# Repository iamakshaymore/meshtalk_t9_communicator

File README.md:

<div align="center" markdown="1">

<h1>Meshtastic Firmware</h1>

</div>

</div>

<div align="center">
	<a href="https://meshtastic.org">Website</a>
	-
	<a href="https://meshtastic.org/docs/">Documentation</a>
</div>

## Overview

**This is a fork of the official Meshtastic firmware** with custom UI implementation currently working on:
- **Heltec WiFi LoRa 32 V3**
- **Heltec WiFi LoRa 32 V4**
- **MeshTalk T9** (Custom PCB - MESHTASTIC Build-Off 2026 Entry)

This fork adds a custom keyboard-driven UI with T9 input, LoRa network visualization, and message management capabilities using a 4x4 matrix keypad and TFT display.

### Hardware Configuration

#### Heltec V3 Custom Pin Configuration

**TFT Display (ST7789 240x320):**
- CS: GPIO 10
- DC: GPIO 11  
- RST: GPIO 12
- Backlight: GPIO 13
- SPI: VSPI (MOSI: 35, SCK: 36)

**4x4 Matrix Keypad:**
- Rows: GPIO 14, 15, 16, 17
- Cols: GPIO 4, 5, 6, 7

**Power & Battery:**
- VEXT Enable: GPIO 18 (active low)
- Battery Pin: GPIO 1 (ADC)
- ADC Channel: ADC_CHANNEL_0

#### Heltec V4 Custom Pin Configuration

**TFT Display (ST7789 240x320):**
- CS: GPIO 10
- DC: GPIO 11
- RST: GPIO 12  
- Backlight: GPIO 13
- SPI: VSPI (MOSI: 11, SCK: 14)

**4x4 Matrix Keypad:**
- Rows: GPIO 4, 5, 6, 7
- Cols: GPIO 15, 16, 17, 18

**Power & Battery:**
- VEXT Enable: GPIO 36 (active high, always on - powers GC1109 LDO)
- Battery Pin: GPIO 1 (ADC)
- ADC Channel: ADC_CHANNEL_0

#### MeshTalk T9 Custom Pin Configuration (MESHTASTIC Build-Off 2026 🏆)

**Hardware Platform:**
- **MCU:** ESP32-S3-WROOM-1-N16R8 (16MB Flash, 8MB PSRAM)
- **LoRa Module:** Seeed Wio-SX1262
- **Display:** ST7789 TFT (240x320) via LovyanGFX
- **Input:** 4x4 Matrix Keypad
- **Form Factor:** Custom PCB design with integrated components

**LoRa Configuration (Wio-SX1262):**
- MISO: GPIO 11
- MOSI: GPIO 12
- SCK: GPIO 13
- CS: GPIO 21
- Reset: GPIO 14
- DIO1: GPIO 9
- BUSY: GPIO 10
- RF Switch: DIO2 controlled
- TCXO: 1.8V

**Power & Battery:**
- Battery ADC: GPIO 8 (ADC_CHANNEL_7)
- ADC Control: GPIO 47 (enable/disable to save power)
- ADC Multiplier: 4.9 (390kΩ/10kΩ voltage divider)
- ADC Attenuation: 2.5dB
- Boot Button: GPIO 0 (hardware pull-up)

**Flash & Memory:**
- 16MB Flash (QIO mode, 80MHz)
- 8MB Octal SPI PSRAM (QIO OPI mode)
- Custom 16MB partition scheme

**Project Links:**
- 📁 Hardware Design: `meshtastic-build-off-2026/Hardware/meshtalk_t9/`
- 🎬 Demo Video: [YouTube](https://www.youtube.com/watch?v=elmYMMCQKS4)
- 📸 Photos & Schematics: `meshtastic-build-off-2026/Demo/`

### Features

- Custom T9 text input system for efficient messaging
- LoRa network node visualization with signal strength indicators
- Message management (send/receive/view history)
- Direct messaging and channel messaging support
- Favorites management
- Battery monitoring and power management
- Bluetooth disabled for reduced power consumption

## MESHTASTIC Build-Off 2026 Status 🏆

This project is my entry for the **MESHTASTIC Build-Off 2026** competition featuring the **MeshTalk T9** - a custom hardware device with integrated display and keypad.

### Phase 1: Custom PCB Design ✅ **COMPLETE**
- ✅ Designed custom PCB using **ESP32-S3-WROOM-1-N16R8** (16MB Flash, 8MB PSRAM)
- ✅ Integrated **Seeed Wio-SX1262** LoRa module
- ✅ Optimized board layout with RF considerations
- ✅ Integrated keypad matrix and display connections on-board
- ✅ Implemented power management with battery charging circuitry
- ✅ PCB manufactured and assembled successfully

### Phase 2: Firmware Adaptation ✅ **COMPLETE**
- ✅ Ported custom UI module to MeshTalk T9 hardware
- ✅ Updated pin configurations for custom PCB (`variants/esp32s3/meshtalk_t9/`)
- ✅ Configured SX1262 LoRa radio with proper RF switching
- ✅ Implemented battery monitoring with ADC control for power savings
- ✅ Created custom variant configuration with 16MB partition scheme
- ✅ Device boots and runs Meshtastic firmware successfully

### Phase 3: Testing & Validation ✅ **COMPLETE**
- ✅ Extensive testing similar to Heltec V3/V4 validation
- ✅ Range testing and mesh network performance benchmarks
- ✅ Power consumption analysis and optimization
- ✅ UI/UX testing with physical hardware
- ✅ Field testing in real-world scenarios
- ✅ Documentation and competition submission preparation

## Building the Firmware

### For Heltec V3 Custom
```bash
platformio run -e heltec-v3-custom
platformio run -e heltec-v3-custom -t upload
```

### For Heltec V4 Custom
```bash
platformio run -e heltec-v4-custom
platformio run -e heltec-v4-custom -t upload
```

### For MeshTalk T9 (Build-Off 2026 Entry)
```bash
# Build firmware
platformio run -e meshtalk-t9

# Upload to device
platformio run -e meshtalk-t9 -t upload --upload-port /dev/cu.usbmodem101

# Erase flash and upload (for first-time flash or troubleshooting)
platformio run -e meshtalk-t9 -t erase_upload

# Monitor serial output
platformio device monitor -p /dev/cu.usbmodem101
```

### Get Started

- 🔧 **[Original Meshtastic Firmware](https://github.com/meshtastic/firmware)** – Upstream repository
- 📖 **[Building Instructions](https://meshtastic.org/docs/development/firmware/build)** - Learn how to compile the firmware from source.
- ⚡ **[Flashing Instructions](https://meshtastic.org/docs/getting-started/flashing-firmware/)** - Install or update the firmware on your device.

Join the Meshtastic community and help improve the project! 🚀

## Stats

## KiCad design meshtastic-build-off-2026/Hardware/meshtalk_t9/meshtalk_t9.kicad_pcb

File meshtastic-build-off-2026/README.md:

# MESHTASTIC Build-Off 2026 - Hardware Design

## Project Overview

This directory contains the custom hardware design for the **MESHTASTIC Build-Off 2026** competition entry. The goal is to create a custom PCB-based Meshtastic device with integrated display and keypad interface.

## PCB Renders

<table>
<tr>
<td width="50%">

**Front**

</td>
<td width="50%">

**Back**

</td>
</tr>
</table>

## Schematics

<table>
<tr>
<td width="50%">

**ESP32-S3 Core**

</td>
<td width="50%">

**LoRa Module**

</td>
</tr>
<tr>
<td width="50%">

**User Interface**

</td>
<td width="50%">

**Power Management**

</td>
</tr>
</table>

## Device Photos

### Assembled Device

<table>
<tr>
<td width="50%">

</td>
<td width="50%">

</td>
</tr>
<tr>
<td width="50%">

</td>
<td width="50%">

</td>
</tr>
</table>

## Device Demonstration

### Video Walkthrough

**[▶️ Click to watch the full device demonstration on Youtube](https://www.youtube.com/watch?v=elmYMMCQKS4)**

*Device demonstration showing the T9 interface, messaging, and LoRa mesh functionality*

## Competition Entry

- **Event:** MESHTASTIC Build-Off 2026
- **Category:** Custom Hardware Design
- **Project Status:** Complete - Ready for Competition

## Hardware Specifications

### Core Components

- **Microcontroller:** ESP32-S3
  - Dual-core processor
  - Built-in WiFi support
  - Low power consumption
  - Ample GPIO for peripherals

- **LoRa Module:** Wio-SX1262 Wireless Module
  - Sub-GHz LoRa transceiver
  - Long-range mesh networking capability
  - Optimized for low power operation

### Peripheral Integration

- **Display:** TFT ST7789 (240x320 pixels)
  - Custom UI with LoRa network visualization
  - Message management interface
  - Battery and signal indicators

- **Input:** 4x4 Matrix Keypad
  - T9 text input system
  - Navigation and control keys
  - Efficient one-handed operation

- **Power Management:**
  - LiPo battery support with charging circuit
  - Power monitoring and low-battery alerts
  - Optimized sleep modes

## Design Goals

1. **Integration:** Single PCB design combining all components
2. **Efficiency:** Low power consumption for extended battery life
3. **Usability:** Intuitive keypad-based interface
4. **Reliability:** Robust design suitable for outdoor/field use
5. **Compliance:** Meet MESHTASTIC Build-Off 2026 requirements

## Development Phases

### Phase 1: PCB Design ⚡ (Completed)
- [x] Schematic design (Done Jun 19, 2026)
- [x] Component selection and sourcing (Done Jun 19, 2026)
- [x] PCB layout and routing (Done Jun 19, 2026)
- [x] Power circuit design (Done Jun 19, 2026)
- [x] Antenna integration planning (Done Jun 19, 2026)

### Phase 2: Firmware Adaptation 🔧 (Completed)
- [x] Port custom UI to new hardware (Done Aug 2026)
- [x] Update pin configurations (Done Aug 2026)
- [x] Test and optimize power management (Done Aug 2026)
- [x] Create custom variant configuration (Done Aug 2026)

### Phase 3: Testing & Validation ✅ (Completed)
- [x] Prototype assembly and bring-up (Done Aug 2026)
- [x] Hardware functionality testing (Done Aug 2026)
- [x] Range and mesh network testing (Done Aug 2026)
- [x] Power consumption analysis (Done Aug 2026)
- [x] Field testing and optimization (Done Aug 2026)

## Bill of Materials (BOM)

| Order | Reference | MPN/SKU | Quantity | Unit Cost | Description |
|-------|-----------|---------|----------|-----------|-------------|
| 1 | C2, C3, C6 | 302010165 | 3 | $0.06 | Capacitors |
| 2 | R9 | 301010367 | 1 | $0.01 | Resistor |
| 3 | R7 | 301010680 | 1 | $0.01 | Resistor |
| 4 | R2, R3 | 301012180 | 2 | $0.01 | Resistors |
| 5 | R1, R10, R11 | 301010361 | 3 | $0.01 | Resistors |
| 6 | R4, R6, R8 | 301010396 | 3 | $0.01 | Resistors |
| 7 | R5 | RC0805FR-07390KL | 1 | $0.23 | 390K Resistor |
| 8 | C1, C4, C5 | 302010361 | 3 | $0.05 | Capacitors |
| 9 | Q1, Q3 | 305031702 | 2 | $0.30 | Transistors |
| 10 | Q2 | 305030028 | 1 | $0.13 | Transistor |
| 11 | U5 | AP7361C-33E-13 | 1 | $2.20 | 3.3V Voltage Regulator |
| 12 | J2 | 53261-0271 | 1 | $0.98 | Connector |
| 13 | D1 | 304020028 | 1 | $0.40 | Diode |
| 14 | U1 | ESP32-S3-WROOM-1-N16R8 | 1 | $6.35 | ESP32-S3 MCU (16MB Flash, 8MB PSRAM) |
| 15 | D2 | 17-215/GHC-YR1S2/3T | 1 | $2.32 | LED |
| 16 | U3 | MCP73831T-2ACI/MC | 1 | $1.18 | Li-Po Battery Charger IC |
| 17 | SW2-SW17 | B3FS-1002P | 16 | $0.83 | Tactile Switches (4x4 Keypad) |
| 18 | SW1, SW18 | KMR221G LFS | 2 | $3.13 | Tactile Switches (Reset/Boot) |
| 19 | J1 | 320010859 | 1 | $0.75 | Connector (USB-C) |
| 20 | U2 | USBLC6-2SC6 | 1 | $2.59 | USB ESD Protection IC |
| 21 | U4 | 114993390 | 1 | $21.45 | LoRa Module/Display Module |

### Additional Components (Not in PCB Assembly)

| Component | Description | Quantity | Notes |
|-----------|-------------|----------|-------|
| **Display** | ST7789 TFT LCD 240x320 | 1 | 2.4" color display |
| **Battery** | Li-Po 3.7V 2000mAh | 1 | Rechargeable battery |
| **Antenna** | 868/915MHz LoRa Antenna | 1 | External SMA or U.FL |

### Cost Summary

- **PCB Components:** ~$98.88 per unit (based on 5-unit order)
- **Additional Parts:** ~$15-25 (display, battery, antenna, enclosure)
- **PCB Manufacturing:** ~$10-20 per unit (depending on quantity)
- **Assembly:** DIY or ~$30-50 professional assembly

**Total Estimated Cost per Unit:** ~$124-194

*Note: Prices based on small quantity orders (5 units). Costs decrease significantly with larger production runs.*

---

**Competition Preparation Status:** Complete  
**Last Updated:** August 2026

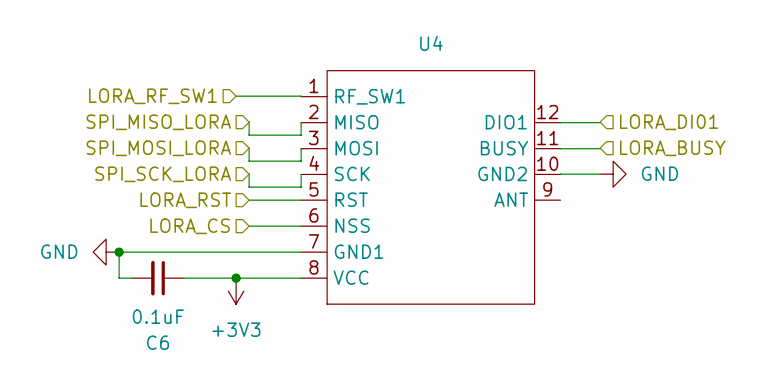
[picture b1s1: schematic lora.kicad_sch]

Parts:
C6: 0.1uF; C_0805_2012Metric; MPN CC0805KRX7R9BB104
U4: Wio-SX1262; Wio SX1262; MPN Wio-SX1262

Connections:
+3V3: C6.1, U4.8 (VCC); also elsewhere on the board
/LoRa_Radio/LORA_BUSY: U4.11 (BUSY); also elsewhere on the board
/LoRa_Radio/LORA_CS: U4.6 (NSS); also elsewhere on the board
/LoRa_Radio/LORA_DI01: U4.12 (DIO1); also elsewhere on the board
/LoRa_Radio/LORA_RF_SW1: U4.1 (RF_SW1); also elsewhere on the board
/LoRa_Radio/LORA_RST: U4.5 (RST); also elsewhere on the board
/LoRa_Radio/SPI_MISO_LORA: U4.2 (MISO); also elsewhere on the board
/LoRa_Radio/SPI_MOSI_LORA: U4.3 (MOSI); also elsewhere on the board
/LoRa_Radio/SPI_SCK_LORA: U4.4 (SCK); also elsewhere on the board
GND: C6.2, U4.7 (GND1), U4.10 (GND2); also elsewhere on the board

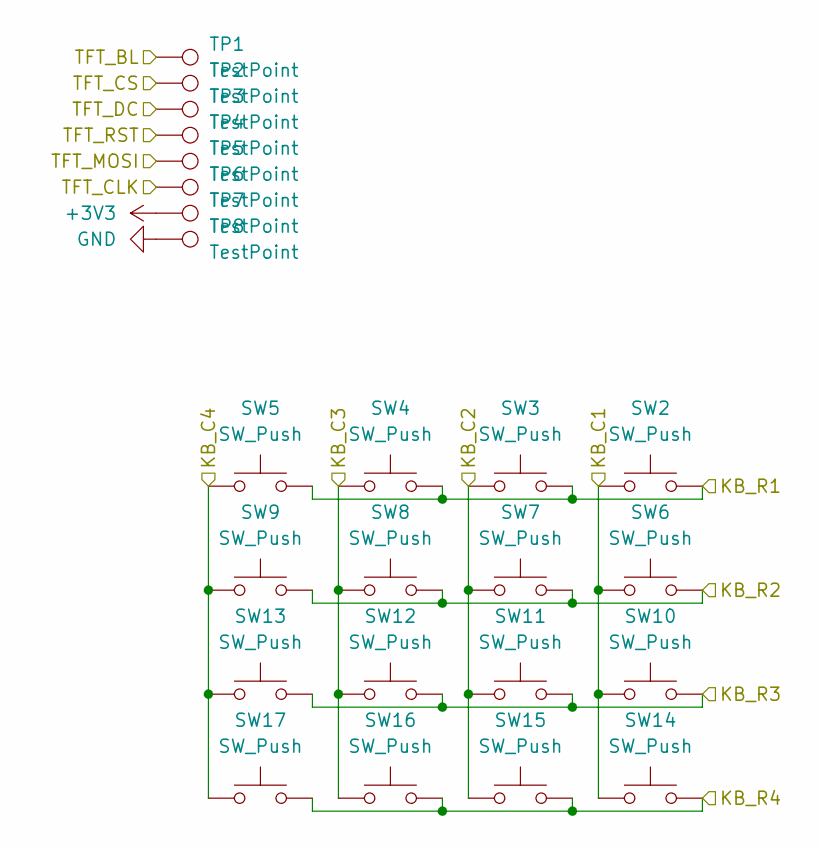
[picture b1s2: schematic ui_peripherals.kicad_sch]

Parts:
SW2, SW3, SW4, SW5, SW6, SW7, SW8, SW9, SW10, SW11, SW12, SW13, SW14, SW15, SW16, SW17: SW_Push; SW_SPST_Omron_B3FS-100xP; MPN B3FS-1002P
TP1, TP2, TP3, TP4, TP5, TP6, TP7, TP8: TestPoint; TestPoint_Pad_D1.0mm

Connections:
+3V3: TP7.1; also elsewhere on the board
/MCU_Core/KB_C1: SW2.2, SW6.2, SW10.2, SW14.2; also elsewhere on the board
/MCU_Core/KB_C2: SW3.2, SW7.2, SW11.2, SW15.2; also elsewhere on the board
/MCU_Core/KB_C3: SW4.2, SW8.2, SW12.2, SW16.2; also elsewhere on the board
/MCU_Core/KB_C4: SW5.2, SW9.2, SW13.2, SW17.2; also elsewhere on the board
/MCU_Core/KB_R1: SW2.1, SW3.1, SW4.1, SW5.1; also elsewhere on the board
/MCU_Core/KB_R2: SW6.1, SW7.1, SW8.1, SW9.1; also elsewhere on the board
/MCU_Core/KB_R3: SW10.1, SW11.1, SW12.1, SW13.1; also elsewhere on the board
/MCU_Core/KB_R4: SW14.1, SW15.1, SW16.1, SW17.1; also elsewhere on the board
/MCU_Core/TFT_BL: TP1.1; also elsewhere on the board
/MCU_Core/TFT_CLK: TP6.1; also elsewhere on the board
/MCU_Core/TFT_CS: TP2.1; also elsewhere on the board
/MCU_Core/TFT_DC: TP3.1; also elsewhere on the board
/MCU_Core/TFT_MOSI: TP5.1; also elsewhere on the board
/MCU_Core/TFT_RST: TP4.1; also elsewhere on the board
GND: TP8.1; also elsewhere on the board

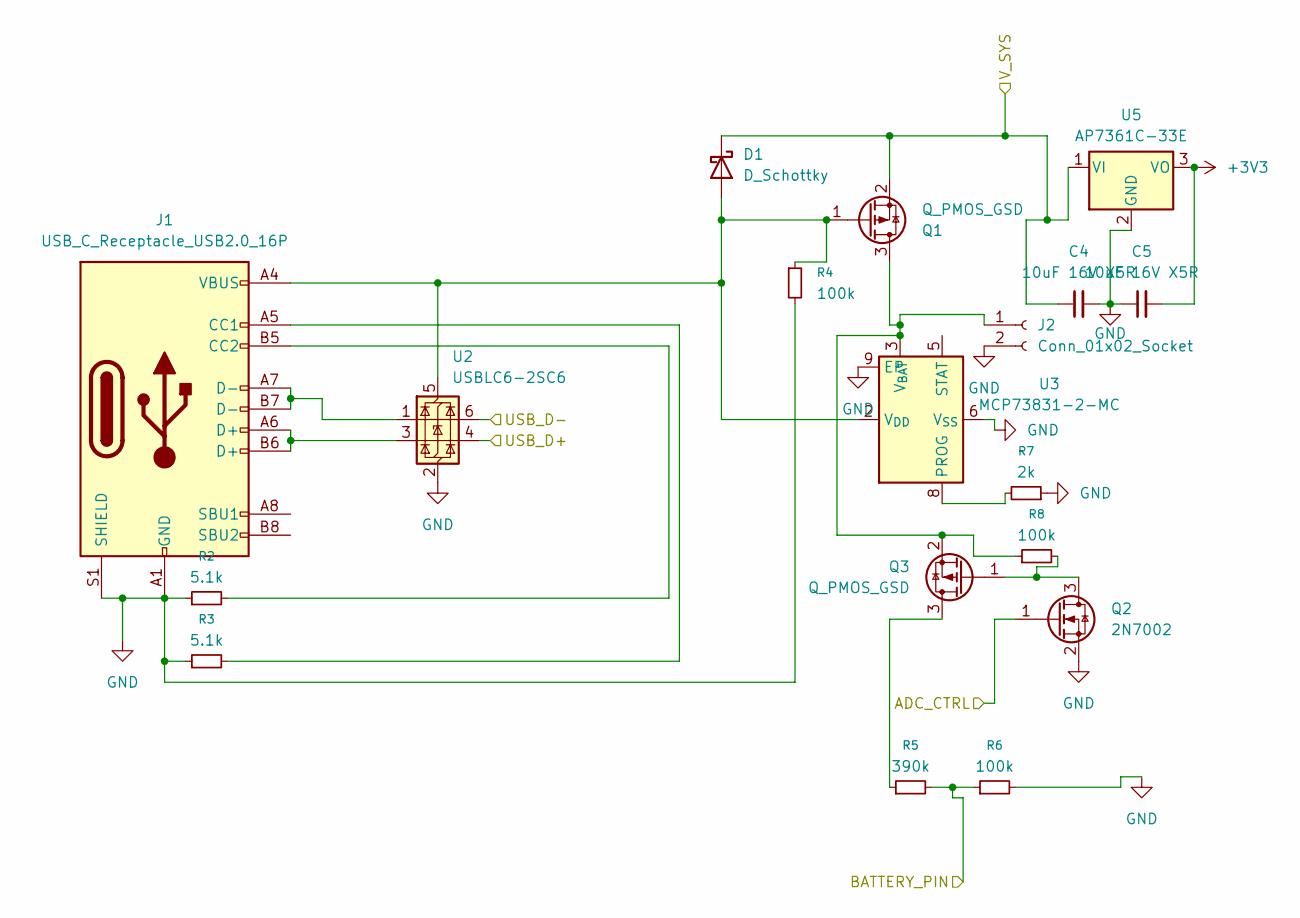
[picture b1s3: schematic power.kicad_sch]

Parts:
C4, C5: 10uF 16V X5R; C_0805_2012Metric; MPN CL21A106KOQNNNE
D1: D_Schottky; D_SOD-123; MPN MBR0520LT1G
J1: USB_C_Receptacle_USB2.0_16P; USB_C_Receptacle_HRO_TYPE-C-31-M-12; MPN TYPE-C-31-M-12
J2: Conn_01x02_Socket; Molex_PicoBlade_53261-0271_1x02-1MP_P1.25mm_Horizontal; MPN 53261-0271
Q1, Q3: Q_PMOS_GSD; SOT-23; MPN AO3401A
Q2: 2N7002; SOT-23; MPN 2N7002,215
R2, R3: 5.1k; R_0805_2012Metric; MPN RC0805FR-075K1L
R4, R6, R8: 100k; R_0805_2012Metric; MPN RC0805FR-07100KL
R5: 390k; R_0805_2012Metric; MPN RC0805FR-07390KL
R7: 2k; R_0805_2012Metric; MPN RC0805FR-072KL
U2: USBLC6-2SC6; SOT-23-6; MPN USBLC6-2SC6
U3: MCP73831-2-MC; DFN-8-1EP_3x2mm_P0.5mm_EP1.7x1.4mm; MPN MCP73831T-2ACI/MC
U5: AP7361C-33E; SOT-223-3_TabPin2; MPN AP7361C-33E-13

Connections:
+3V3: C5.2, U5.3 (VO); also elsewhere on the board
/MCU_Core/ADC_CTRL: Q2.1 (G); also elsewhere on the board
/MCU_Core/BATTERY_PIN: R5.2, R6.1; also elsewhere on the board
/MCU_Core/USB_D+: U2.4 (I/O2); also elsewhere on the board
/MCU_Core/USB_D-: U2.6 (I/O1); also elsewhere on the board
/Power_Management/V_SYS: C4.1, D1.1 (K), Q1.2 (S), U5.1 (VI)
GND: C4.2, C5.1, J1.A1 (GND), J1.A12 (GND), J1.B1 (GND), J1.B12 (GND), J1.S1 (SHIELD), J2.2, Q2.2 (S), R2.1, R3.1, R4.2, R6.2, R7.1, U2.2 (GND), U3.6 (V_{SS}), U3.9 (EP), U5.2 (GND); also elsewhere on the board
unnamed: D1.2 (A), J1.A4 (VBUS), J1.A9 (VBUS), J1.B4 (VBUS), J1.B9 (VBUS), Q1.1 (G), R4.1, U2.5 (VBUS), U3.1 (V_{DD}), U3.2 (V_{DD})
unnamed: J1.A5 (CC1), R3.2
unnamed: J1.B5 (CC2), R2.2
unnamed: J1.A6 (D+), J1.B6 (D+), U2.3 (I/O2)
unnamed: J1.A7 (D-), J1.B7 (D-), U2.1 (I/O1)
unnamed: J2.1, Q1.3 (D), Q3.2 (S), R8.1, U3.3 (V_{BAT}), U3.4 (V_{BAT})
unnamed: Q2.3 (D), Q3.1 (G), R8.2
unnamed: Q3.3 (D), R5.1
unnamed: R7.2, U3.8 (PROG)

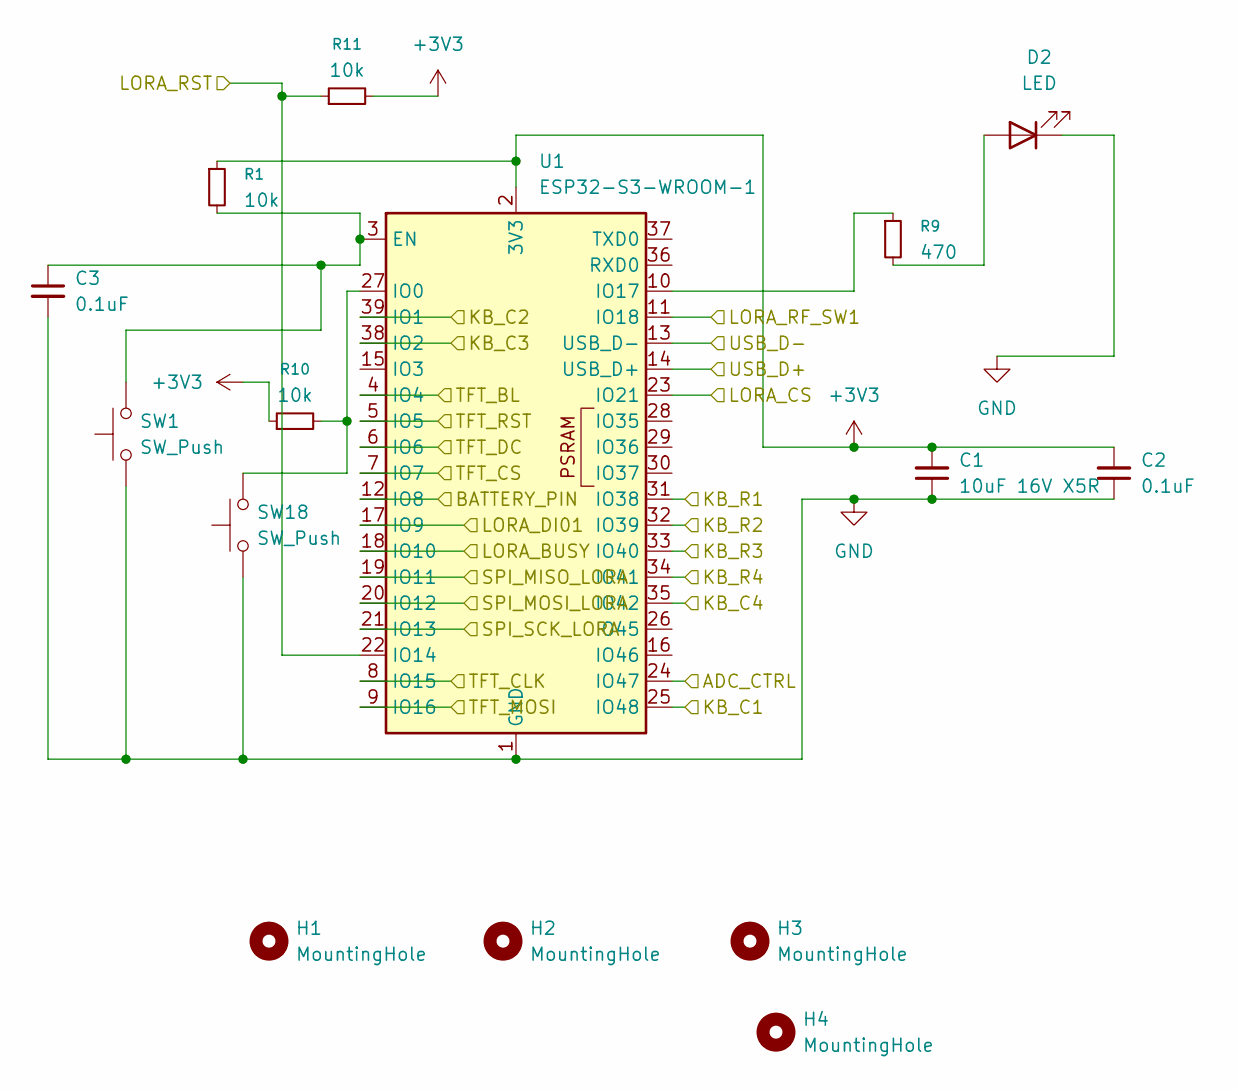
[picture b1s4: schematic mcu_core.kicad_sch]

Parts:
C1: 10uF 16V X5R; C_0805_2012Metric; MPN CL21A106KOQNNNE
C2, C3: 0.1uF; C_0805_2012Metric; MPN CC0805KRX7R9BB104
D2: LED; LED_0805_2012Metric; MPN 17-215/GHC-YR1S2/3T
H1, H2, H3, H4: MountingHole; MountingHole_2.2mm_M2
R1, R10, R11: 10k; R_0805_2012Metric; MPN RC0805FR-0710KL
R9: 470; R_0805_2012Metric; MPN RC0805FR-07470RL
SW1, SW18: SW_Push; SW_Push_1P1T_NO_CK_KMR2; MPN KMR221G LFS
U1: ESP32-S3-WROOM-1; MPN ESP32-S3-WROOM-1-N16R8

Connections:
+3V3: C1.2, C2.2, R1.1, R10.1, R11.2, U1.2 (3V3); also elsewhere on the board
/LoRa_Radio/LORA_BUSY: U1.18 (IO10); also elsewhere on the board
/LoRa_Radio/LORA_CS: U1.23 (IO21); also elsewhere on the board
/LoRa_Radio/LORA_DI01: U1.17 (IO9); also elsewhere on the board
/LoRa_Radio/LORA_RF_SW1: U1.11 (IO18); also elsewhere on the board
/LoRa_Radio/LORA_RST: R11.1, U1.22 (IO14); also elsewhere on the board
/LoRa_Radio/SPI_MISO_LORA: U1.19 (IO11); also elsewhere on the board
/LoRa_Radio/SPI_MOSI_LORA: U1.20 (IO12); also elsewhere on the board
/LoRa_Radio/SPI_SCK_LORA: U1.21 (IO13); also elsewhere on the board
/MCU_Core/ADC_CTRL: U1.24 (IO47); also elsewhere on the board
/MCU_Core/BATTERY_PIN: U1.12 (IO8); also elsewhere on the board
/MCU_Core/KB_C1: U1.25 (IO48); also elsewhere on the board
/MCU_Core/KB_C2: U1.39 (IO1); also elsewhere on the board
/MCU_Core/KB_C3: U1.38 (IO2); also elsewhere on the board
/MCU_Core/KB_C4: U1.35 (IO42); also elsewhere on the board
/MCU_Core/KB_R1: U1.31 (IO38); also elsewhere on the board
/MCU_Core/KB_R2: U1.32 (IO39); also elsewhere on the board
/MCU_Core/KB_R3: U1.33 (IO40); also elsewhere on the board
/MCU_Core/KB_R4: U1.34 (IO41); also elsewhere on the board
/MCU_Core/TFT_BL: U1.4 (IO4); also elsewhere on the board
/MCU_Core/TFT_CLK: U1.8 (IO15); also elsewhere on the board
/MCU_Core/TFT_CS: U1.7 (IO7); also elsewhere on the board
/MCU_Core/TFT_DC: U1.6 (IO6); also elsewhere on the board
/MCU_Core/TFT_MOSI: U1.9 (IO16); also elsewhere on the board
/MCU_Core/TFT_RST: U1.5 (IO5); also elsewhere on the board
/MCU_Core/USB_D+: U1.14 (USB_D+); also elsewhere on the board
/MCU_Core/USB_D-: U1.13 (USB_D-); also elsewhere on the board
GND: C1.1, C2.1, C3.2, D2.1 (K), SW1.1, SW18.1, U1.1 (GND), U1.40 (GND), U1.41 (GND); also elsewhere on the board
unnamed: D2.2 (A), R9.2
unnamed: C3.1, R1.2, SW1.2, U1.3 (EN)
unnamed: R10.2, SW18.2, U1.27 (IO0)
unnamed: R9.1, U1.10 (IO17)

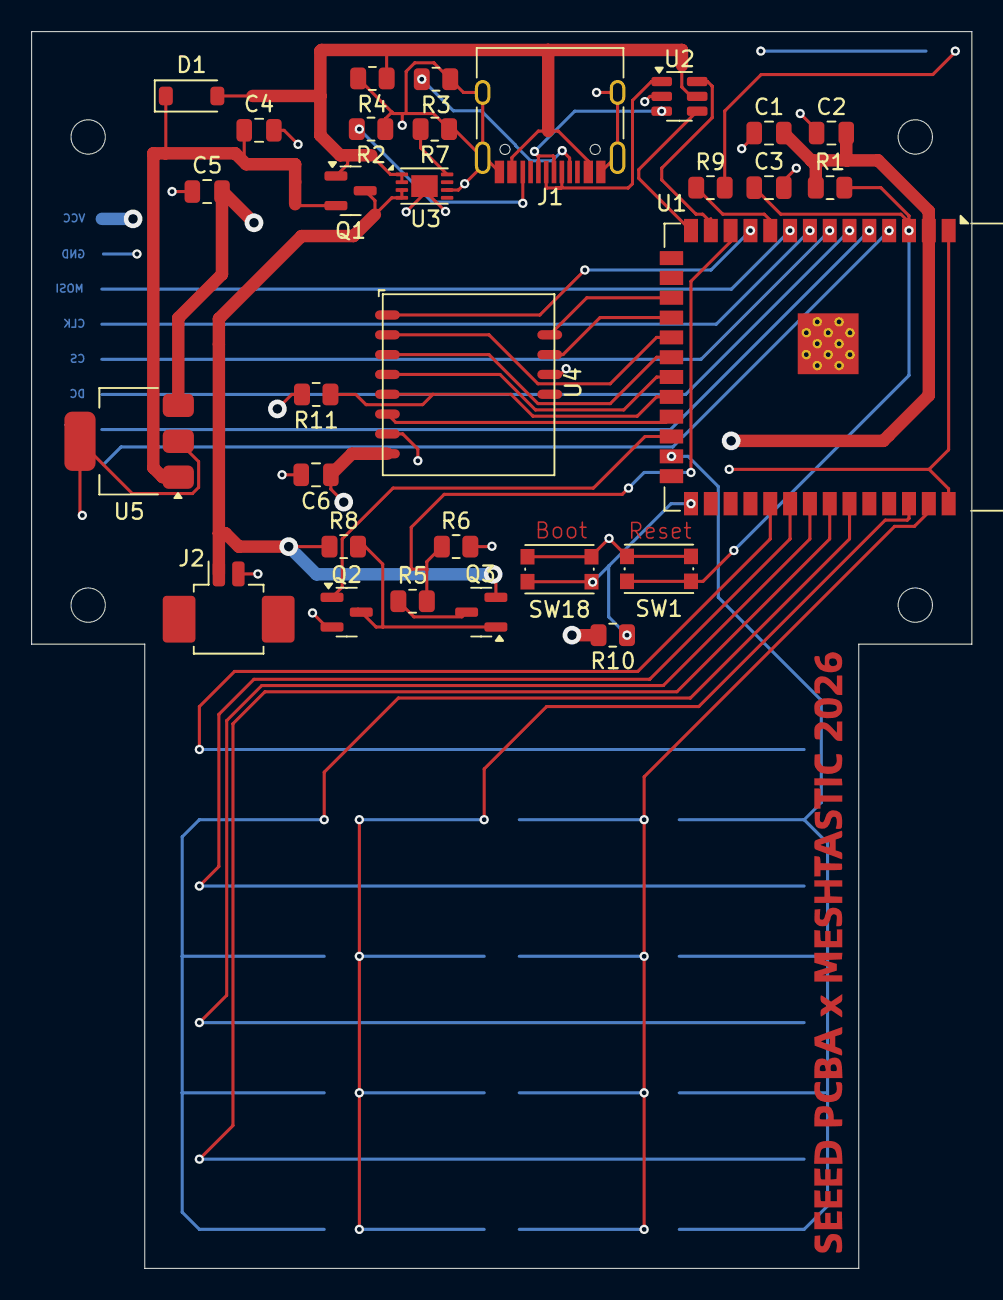
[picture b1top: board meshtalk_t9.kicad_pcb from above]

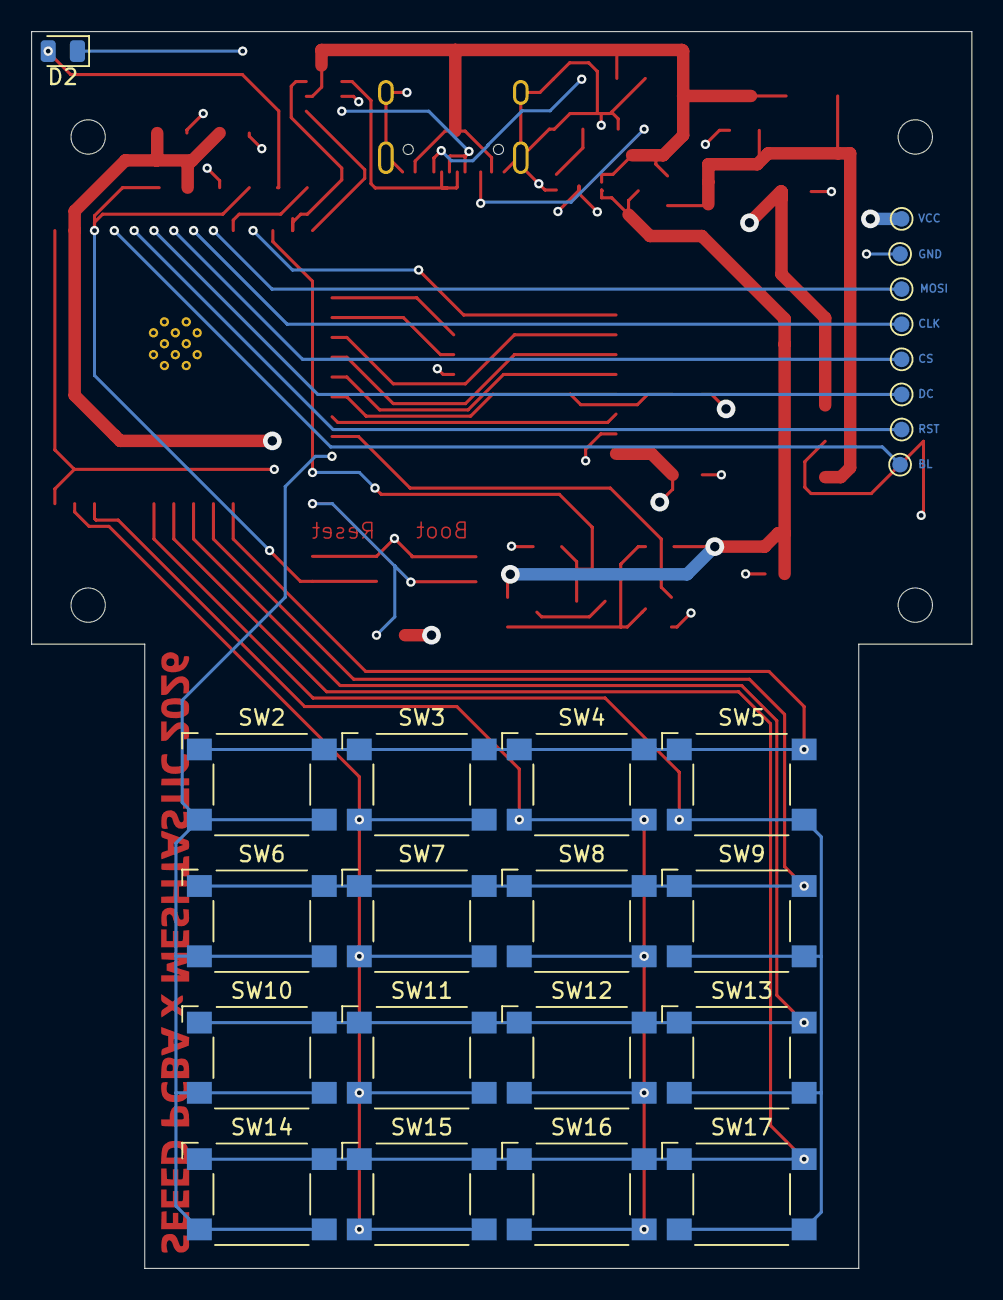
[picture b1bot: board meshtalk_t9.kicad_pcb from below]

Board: 4 copper layers, 60.2 x 79.2 mm, 59 parts (25 on the bottom side), 42 nets.

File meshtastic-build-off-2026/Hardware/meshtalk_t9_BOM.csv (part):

"Reference","Qty","Value","DNP","Exclude from BOM","Exclude from Board","Footprint","Datasheet","Manufacturer","Description","MPN"
"C2","1","0.1uF","","","","Capacitor_SMD:C_0805_2012Metric","~","YAGEO","Unpolarized capacitor, small symbol","CC0805KRX7R9BB104"
"C3","1","0.1uF","","","","Capacitor_SMD:C_0805_2012Metric","~","YAGEO","Unpolarized capacitor, small symbol","CC0805KRX7R9BB104"
"C6","1","0.1uF","","","","Capacitor_SMD:C_0805_2012Metric","~","YAGEO","Unpolarized capacitor, small symbol","CC0805KRX7R9BB104"
"R9","1","470","","","","Resistor_SMD:R_0805_2012Metric","~","YAGEO","Resistor, small symbol","RC0805FR-07470RL"
"R7","1","2k","","","","Resistor_SMD:R_0805_2012Metric","~","YAGEO","Resistor, small symbol","RC0805FR-072KL"
"R2","1","5.1k","","","","Resistor_SMD:R_0805_2012Metric","~","YAGEO","Resistor, small symbol","RC0805FR-075K1L"
"R3","1","5.1k","","","","Resistor_SMD:R_0805_2012Metric","~","YAGEO","Resistor, small symbol","RC0805FR-075K1L"
"R1","1","10k","","","","Resistor_SMD:R_0805_2012Metric","~","YAGEO","Resistor, small symbol","RC0805FR-0710KL"
"R10","1","10k","","","","Resistor_SMD:R_0805_2012Metric","~","YAGEO","Resistor, small symbol","RC0805FR-0710KL"
"R11","1","10k","","","","Resistor_SMD:R_0805_2012Metric","~","YAGEO","Resistor, small symbol","RC0805FR-0710KL"
"R4","1","100k","","","","Resistor_SMD:R_0805_2012Metric","~","YAGEO","Resistor, small symbol","RC0805FR-07100KL"
"R6","1","100k","","","","Resistor_SMD:R_0805_2012Metric","~","YAGEO","Resistor, small symbol","RC0805FR-07100KL"
"R8","1","100k","","","","Resistor_SMD:R_0805_2012Metric","~","YAGEO","Resistor, small symbol","RC0805FR-07100KL"
"R5","1","390k","","","","Resistor_SMD:R_0805_2012Metric","~","YAGEO","Resistor, small symbol","RC0805FR-07390KL"
"C1","1","10uF 16V X5R","","","","Capacitor_SMD:C_0805_2012Metric","~","Samsung","Unpolarized capacitor, small symbol","CL21A106KOQNNNE"
"C4","1","10uF 16V X5R","","","","Capacitor_SMD:C_0805_2012Metric","~","Samsung","Unpolarized capacitor, small symbol","CL21A106KOQNNNE"
"C5","1","10uF 16V X5R","","","","Capacitor_SMD:C_0805_2012Metric","~","Samsung","Unpolarized capacitor, small symbol","CL21A106KOQNNNE"
"Q2","1","2N7002","","","","Package_TO_SOT_SMD:SOT-23","https://www.onsemi.com/pub/Collateral/NDS7002A-D.PDF","Nexperia","0.115A Id, 60V Vds, N-Channel MOSFET, SOT-23","2N7002,215"
"U5","1","AP7361C-33E","","","","Package_TO_SOT_SMD:SOT-223-3_TabPin2","https://www.diodes.com/assets/Datasheets/AP7361C.pdf","Diodes Inc","1A Low Dropout regulator, positive, 3.3V fixed output, SOT-223","AP7361C-33E-13"
"J2","1","Conn_01x02_Socket","","","","Connector_Molex:Molex_PicoBlade_53261-0271_1x02-1MP_P1.25mm_Horizontal","~","Molex","Generic connector, single row, 01x02, script generated","53261-0271"
"D1","1","D_Schottky","","","","Diode_SMD:D_SOD-123","~","onsemi","Schottky diode","MBR0520LT1G"
"U1","1","ESP32-S3-WROOM-1","","","","RF_Module:ESP32-S3-WROOM-1","https://www.espressif.com/sites/default/files/documentation/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","Espressif","RF Module, ESP32-S3 SoC, Wi-Fi 802.11b/g/n, Bluetooth, BLE, 32-bit, 3.3V, onboard antenna, SMD","ESP32-S3-WROOM-1-N16R16VA"
"D2","1","LED","","","","LED_SMD:LED_0805_2012Metric","~","Everlight","Light emitting diode","17-215/GHC-YR1S2/3T"
"U3","1","MCP73831-2-MC","","","","Package_DFN_QFN:DFN-8-1EP_3x2mm_P0.5mm_EP1.7x1.4mm","http://ww1.microchip.com/downloads/en/DeviceDoc/20001984g.pdf","Microchip","Single cell, Li-Ion/Li-Po charge management controller, 4.20V, Tri-State Status Output, in DFN-8 package","MCP73831T-2ACI/MC"
"H1","1","MountingHole","","Excluded from BOM","","MountingHole:MountingHole_2.2mm_M2","~","","Mounting Hole without connection",""
"H2","1","MountingHole","","Excluded from BOM","","MountingHole:MountingHole_2.2mm_M2","~","","Mounting Hole without connection",""
"H3","1","MountingHole","","Excluded from BOM","","MountingHole:MountingHole_2.2mm_M2","~","","Mounting Hole without connection",""
"H4","1","MountingHole","","Excluded from BOM","","MountingHole:MountingHole_2.2mm_M2","~","","Mounting Hole without connection",""
"Q1","1","Q_PMOS_GSD","","","","Package_TO_SOT_SMD:SOT-23","~","Alpha & Omega","P-MOSFET transistor, gate/source/drain","AO3401A"
"Q3","1","Q_PMOS_GSD","","","","Package_TO_SOT_SMD:SOT-23","~","Alpha & Omega","P-MOSFET transistor, gate/source/drain","AO3401A"
"SW1","1","SW_Push","","","","Button_Switch_SMD:SW_Push_1P1T_NO_CK_KMR2","~","HROparts","Push button switch, generic, two pins","KMR221G LFS"
"SW2","1","SW_Push","","","","Button_Switch_SMD:SW_SPST_Omron_B3FS-100xP","~","Omron","Push button switch, generic, two pins","B3FS-1002P"
"SW3","1","SW_Push","","","","Button_Switch_SMD:SW_SPST_Omron_B3FS-100xP","~","Omron","Push button switch, generic, two pins","B3FS-1002P"
"SW4","1","SW_Push","","","","Button_Switch_SMD:SW_SPST_Omron_B3FS-100xP","~","Omron","Push button switch, generic, two pins","B3FS-1002P"
"SW5","1","SW_Push","","","","Button_Switch_SMD:SW_SPST_Omron_B3FS-100xP","~","Omron","Push button switch, generic, two pins","B3FS-1002P"
"SW6","1","SW_Push","","","","Button_Switch_SMD:SW_SPST_Omron_B3FS-100xP","~","Omron","Push button switch, generic, two pins","B3FS-1002P"
"SW7","1","SW_Push","","","","Button_Switch_SMD:SW_SPST_Omron_B3FS-100xP","~","Omron","Push button switch, generic, two pins","B3FS-1002P"
"SW8","1","SW_Push","","","","Button_Switch_SMD:SW_SPST_Omron_B3FS-100xP","~","Omron","Push button switch, generic, two pins","B3FS-1002P"
"SW9","1","SW_Push","","","","Button_Switch_SMD:SW_SPST_Omron_B3FS-100xP","~","Omron","Push button switch, generic, two pins","B3FS-1002P"
"SW10","1","SW_Push","","","","Button_Switch_SMD:SW_SPST_Omron_B3FS-100xP","~","Omron","Push button switch, generic, two pins","B3FS-1002P"
"SW11","1","SW_Push","","","","Button_Switch_SMD:SW_SPST_Omron_B3FS-100xP","~","Omron","Push button switch, generic, two pins","B3FS-1002P"
"SW12","1","SW_Push","","","","Button_Switch_SMD:SW_SPST_Omron_B3FS-100xP","~","Omron","Push button switch, generic, two pins","B3FS-1002P"
"SW13","1","SW_Push","","","","Button_Switch_SMD:SW_SPST_Omron_B3FS-100xP","~","Omron","Push button switch, generic, two pins","B3FS-1002P"
"SW14","1","SW_Push","","","","Button_Switch_SMD:SW_SPST_Omron_B3FS-100xP","~","Omron","Push button switch, generic, two pins","B3FS-1002P"
"SW15","1","SW_Push","","","","Button_Switch_SMD:SW_SPST_Omron_B3FS-100xP","~","Omron","Push button switch, generic, two pins","B3FS-1002P"
"SW16","1","SW_Push","","","","Button_Switch_SMD:SW_SPST_Omron_B3FS-100xP","~","Omron","Push button switch, generic, two pins","B3FS-1002P"
"SW17","1","SW_Push","","","","Button_Switch_SMD:SW_SPST_Omron_B3FS-100xP","~","Omron","Push button switch, generic, two pins","B3FS-1002P"
"SW18","1","SW_Push","","","","Button_Switch_SMD:SW_Push_1P1T_NO_CK_KMR2","~","HROparts","Push button switch, generic, two pins","KMR221G LFS"
"TP1","1","TestPoint","","Excluded from BOM","","TestPoint:TestPoint_Pad_D1.0mm","~","","test point",""
"TP2","1","TestPoint","","Excluded from BOM","","TestPoint:TestPoint_Pad_D1.0mm","~","","test point",""
"TP3","1","TestPoint","","Excluded from BOM","","TestPoint:TestPoint_Pad_D1.0mm","~","","test point",""
"TP4","1","TestPoint","","Excluded from BOM","","TestPoint:TestPoint_Pad_D1.0mm","~","","test point",""
"TP5","1","TestPoint","","Excluded from BOM","","TestPoint:TestPoint_Pad_D1.0mm","~","","test point",""
"TP6","1","TestPoint","","Excluded from BOM","","TestPoint:TestPoint_Pad_D1.0mm","~","","test point",""
"TP7","1","TestPoint","","Excluded from BOM","","TestPoint:TestPoint_Pad_D1.0mm","~","","test point",""
"TP8","1","TestPoint","","Excluded from BOM","","TestPoint:TestPoint_Pad_D1.0mm","~","","test point",""
"J1","1","USB_C_Receptacle_USB2.0_16P","","","","Connector_USB:USB_C_Receptacle_HRO_TYPE-C-31-M-12","https://www.usb.org/sites/default/files/documents/usb_type-c.zip","HROparts","USB 2.0-only 16P Type-C Receptacle connector","TYPE-C-31-M-12"
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
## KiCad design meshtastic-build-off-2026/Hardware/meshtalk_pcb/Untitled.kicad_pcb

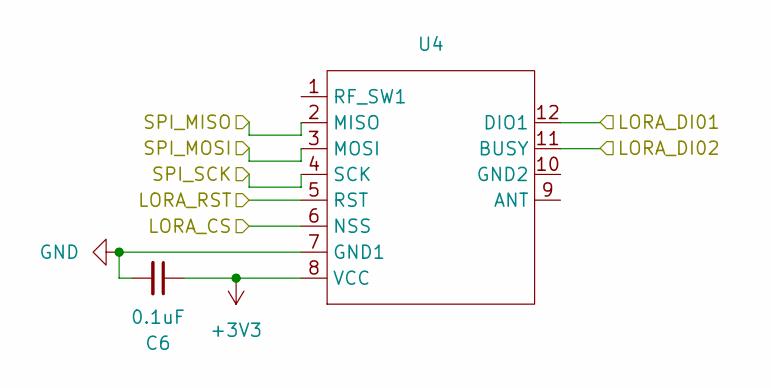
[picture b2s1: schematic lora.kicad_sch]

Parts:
C6: 0.1uF; C_0805_2012Metric
U4: Wio-SX1262; Wio SX1262

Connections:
+3V3: C6.1, U4.8 (VCC); also elsewhere on the board
/LoRa_Radio/LORA_CS: U4.6 (NSS); also elsewhere on the board
/LoRa_Radio/LORA_DI01: U4.12 (DIO1); also elsewhere on the board
/LoRa_Radio/LORA_DI02: U4.11 (BUSY); also elsewhere on the board
/LoRa_Radio/LORA_RST: U4.5 (RST); also elsewhere on the board
/LoRa_Radio/SPI_MISO: U4.2 (MISO); also elsewhere on the board
/LoRa_Radio/SPI_MOSI: U4.3 (MOSI); also elsewhere on the board
/LoRa_Radio/SPI_SCK: U4.4 (SCK); also elsewhere on the board
GND: C6.2, U4.7 (GND1); also elsewhere on the board

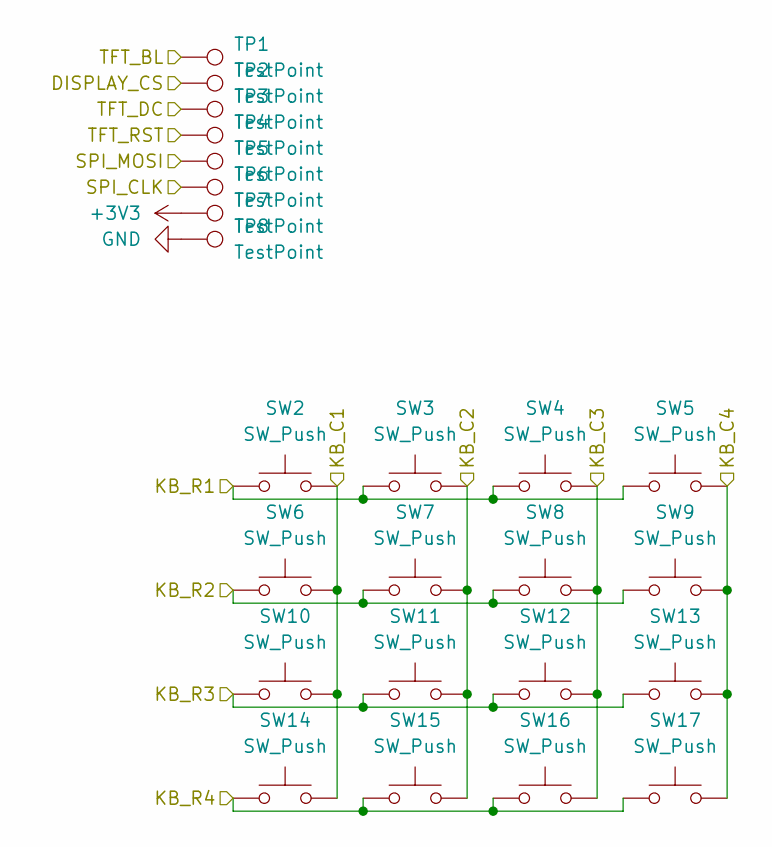
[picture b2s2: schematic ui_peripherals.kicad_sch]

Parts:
SW2, SW3, SW4, SW5, SW6, SW7, SW8, SW9, SW10, SW11, SW12, SW13, SW14, SW15, SW16, SW17: SW_Push; SW_Push_1P1T_NO_CK_KSC6xxJ
TP1, TP2, TP3, TP4, TP5, TP6, TP7, TP8: TestPoint; TestPoint_Pad_D1.0mm

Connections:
+3V3: TP7.1; also elsewhere on the board
/LoRa_Radio/SPI_MOSI: TP5.1; also elsewhere on the board
/LoRa_Radio/SPI_SCK: TP6.1; also elsewhere on the board
/MCU_Core/DISPLAY_CS: TP2.1; also elsewhere on the board
/MCU_Core/KB_C1: SW2.2, SW6.2, SW10.2, SW14.2; also elsewhere on the board
/MCU_Core/KB_C2: SW3.2, SW7.2, SW11.2, SW15.2; also elsewhere on the board
/MCU_Core/KB_C3: SW4.2, SW8.2, SW12.2, SW16.2; also elsewhere on the board
/MCU_Core/KB_C4: SW5.2, SW9.2, SW13.2, SW17.2; also elsewhere on the board
/MCU_Core/KB_R1: SW2.1, SW3.1, SW4.1, SW5.1; also elsewhere on the board
/MCU_Core/KB_R2: SW6.1, SW7.1, SW8.1, SW9.1; also elsewhere on the board
/MCU_Core/KB_R3: SW10.1, SW11.1, SW12.1, SW13.1; also elsewhere on the board
/MCU_Core/KB_R4: SW14.1, SW15.1, SW16.1, SW17.1; also elsewhere on the board
/MCU_Core/TFT_BL: TP1.1; also elsewhere on the board
/MCU_Core/TFT_DC: TP3.1; also elsewhere on the board
/MCU_Core/TFT_RST: TP4.1; also elsewhere on the board
GND: TP8.1; also elsewhere on the board

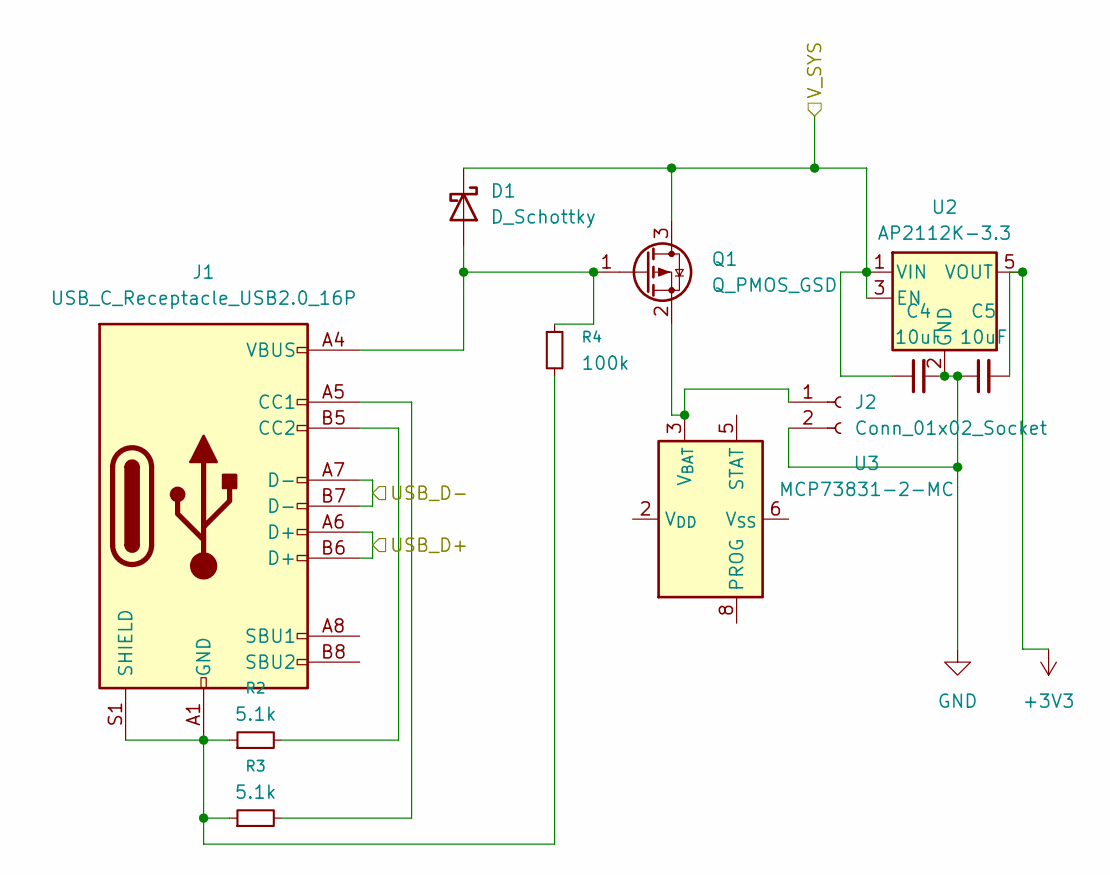
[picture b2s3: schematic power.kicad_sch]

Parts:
C4, C5: 10uF; C_0805_2012Metric
D1: D_Schottky; LED_0805_2012Metric
J1: USB_C_Receptacle_USB2.0_16P; USB_C_Receptacle_HRO_TYPE-C-31-M-12
J2: Conn_01x02_Socket; Molex_PicoBlade_53261-0271_1x02-1MP_P1.25mm_Horizontal
Q1: Q_PMOS_GSD; SOT-23
R2, R3: 5.1k; R_0805_2012Metric
R4: 100k; R_0805_2012Metric
U2: AP2112K-3.3; SOT-23-5
U3: MCP73831-2-MC; DFN-8-1EP_3x2mm_P0.5mm_EP1.7x1.4mm

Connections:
+3V3: C5.2, U2.5 (VOUT); also elsewhere on the board
/MCU_Core/USB_D+: J1.A6 (D+), J1.B6 (D+); also elsewhere on the board
/MCU_Core/USB_D-: J1.A7 (D-), J1.B7 (D-); also elsewhere on the board
/Power_Management/V_SYS: C4.1, D1.1 (K), Q1.3 (D), U2.1 (VIN), U2.3 (EN)
GND: C4.2, C5.1, J2.2, U2.2 (GND); also elsewhere on the board
unnamed: D1.2 (A), J1.A4 (VBUS), J1.A9 (VBUS), J1.B4 (VBUS), J1.B9 (VBUS), Q1.1 (G), R4.1
unnamed: J1.A5 (CC1), R3.2
unnamed: J1.B5 (CC2), R2.2
unnamed: J1.A1 (GND), J1.A12 (GND), J1.B1 (GND), J1.B12 (GND), J1.S1 (SHIELD), R2.1, R3.1, R4.2
unnamed: J2.1, Q1.2 (S), U3.3 (V_{BAT}), U3.4 (V_{BAT})
unnamed: U3.1 (V_{DD}), U3.2 (V_{DD})
